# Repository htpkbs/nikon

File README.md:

# Overview

The nikon is a keyboard PCB.

It has:

* A column-staggered, ortholinear layout
* Low profile Kailh Choc switch spacing
* A split design
* Thumb key clusters
* USB-C
* Symmetry (the same PCB can be used for both left and right halves)

# v1.0 Notes

Capacitors `C1` and `C4` are mislabeled! The silkscreen labels are swapped.

# Key Layout

The key layout looks like this:

This is the raw data that can be pasted into [Keyboard Layout Editor](http://www.keyboard-layout-editor.com/):

```
[{x:3,c:"#2e2e2e",t:"#9c9c9c",a:7},"3",{x:8.5},"8"],
[{y:-0.875,x:2},"2",{x:10.5},"9"],
[{y:-0.875,x:4},"4",{x:6.5},"7"],
[{y:-0.875,x:5},"5",{x:4.5},"6"],
[{y:-0.875},"","1",{x:12.5},"0",""],
[{y:-0.625,x:6,h:1.5},"",{x:2.5,h:1.5},""],
[{y:-0.875,x:3},"E",{x:8.5},"I"],
[{y:-0.875,x:2},"W",{x:10.5},"O"],
[{y:-0.875,x:4},"R",{x:6.5},"U"],
[{y:-0.875,x:5},"T",{x:4.5},"Y"],
[{y:-0.875},"","Q",{x:12.5},"P",""],
[{y:-0.5,x:3},"D",{x:8.5},"K"],
[{y:-0.875,x:2},"S",{x:10.5},"L"],
[{y:-0.875,x:4},"F",{x:6.5},"J"],
[{y:-0.875,x:5},"G",{h:1.5},"",{x:2.5,h:1.5},"","H"],
[{y:-0.875},"","A",{x:12.5},";","'"],
[{y:-0.5,x:3},"C",{x:8.5},","],
[{y:-0.875,x:2},"X",{x:10.5},"."],
[{y:-0.875,x:4},"V",{x:6.5},"M"],
[{y:-0.875,x:5},"B",{x:4.5},"N"],
[{y:-0.875},"Shift","Z",{x:12.5},"/","Shift"],
[{y:-0.375,x:2},"",{x:10.5},""],
[{y:-0.625},"","",{x:12.5},"",""],
[{rx:7.5,ry:4,x:-4.5},""],
[{rx:9,x:3.5},""],
[{r:30,rx:7.5,y:0.75,x:-0.625,w:1.5},""],
[{x:-1.875,h:1.5},"",{h:1.5},"",{h:1.5},""],
[{r:-30,rx:9,y:0.75,x:-0.875,w:1.5},""],
[{x:-1.125,h:1.5},"",{h:1.5},"",{h:1.5},""]
```

# PCB Renders

# Case

Files are in the `case` directory.

# Schematic

[There is a PDF of the schematic here](assets/schematic.pdf).

# AVR Programming

To-do.

## QMK

The nikon uses a port expander (the ATmega MCP23018), similar to the ErgoDox. The firmware will likely be copied from the [Pterodactyl keyboard](https://github.com/qmk/qmk_firmware/tree/master/keyboards/handwired/pterodactyl) since that seems to be the most recent keyboard with a custom `matrix.c` and support for a port expander. Eventually hopefully there will be a [generalized matrix.c for keyboards that use I/O expanders](https://github.com/qmk/qmk_firmware/issues/2065).

# Sublicenses

* The Kailh Choc switch footprints are from the [keyswitch-kicad-libary repository](https://github.com/perigoso/keyswitch-kicad-library). [The CC BY 4.0 license is included here](LICENSE.keyswitch-kicad-library).
* The keyswitch symbols are modified versions from the [MX_Alps_Hybrid repository](https://github.com/ai03-2725/MX_Alps_Hybrid). [The MIT license is included here](LICENSE.MX_Alps_Hybrid).
* The TRRS jack symbol and footprint are not licensed by CUI Devices and are free to use.
* The USB jack symbol and footprint are from SnapEDA (linked from the GCT website) and do not appear to be licensed by GCT.
* The MCP23018 symbol and footprint are from Microchip and are subject to the Ultra Library terms and conditions, which state, "You may incorporate the CONTENT that you are authorized to access into your products or designs which may be distributed without restriction, including for commercial, educational, and open-source purposes."

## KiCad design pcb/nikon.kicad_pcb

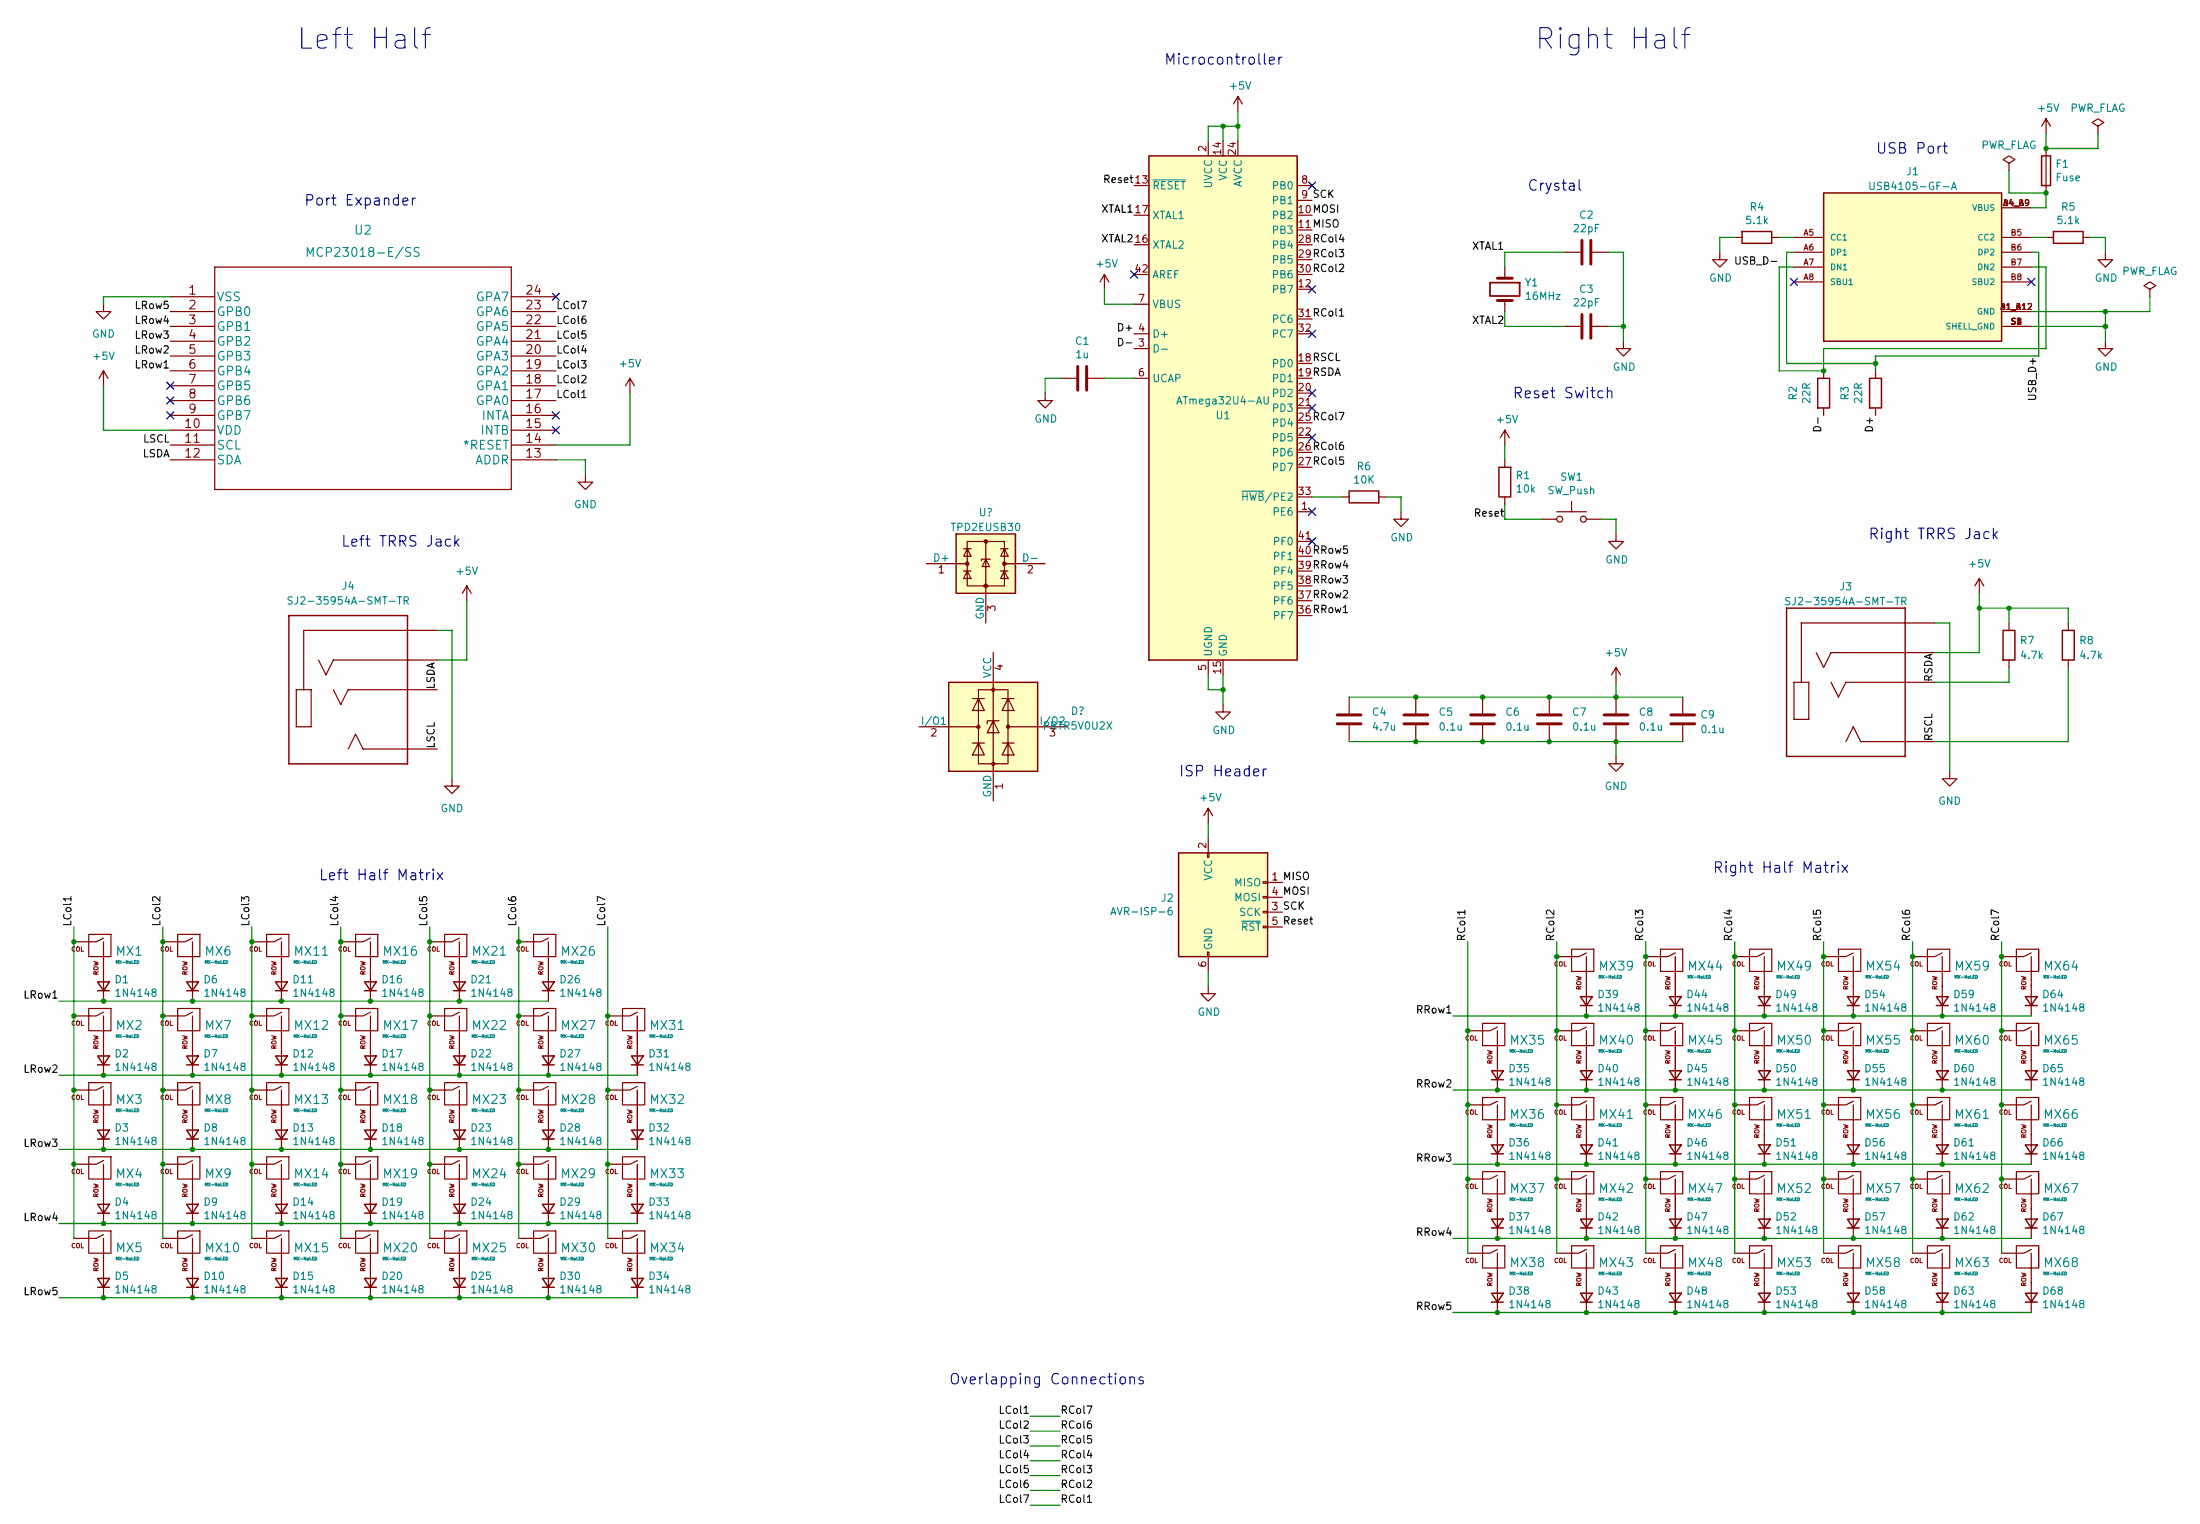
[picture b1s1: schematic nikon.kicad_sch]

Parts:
C1: 1u; C_0805_2012Metric_Pad1.18x1.45mm_HandSolder
C2, C3: 22pF; C_0805_2012Metric_Pad1.18x1.45mm_HandSolder
C4: 4.7u; C_0805_2012Metric_Pad1.18x1.45mm_HandSolder
C5, C6, C7, C8, C9: 0.1u; C_0805_2012Metric_Pad1.18x1.45mm_HandSolder
D1, D2, D3, D4, D5, D6, D7, D8, D9, D10, D11, D12, D13, D14, D15, D16, D17, D18, D19, D20, D21, D22, D23, D24, D25, D26, D27, D28, D29, D30, D31, D32, D33, D34, D35, D36, D37, D38, D39, D40, D41, D42, D43, D44, D45, D46, D47, D48, D49, D50, D51, D52, D53, D54, D55, D56, D57, D58, D59, D60, D61, D62, D63, D64, D65, D66, D67, D68: 1N4148; D_SOD-123F
F1: Fuse; Fuse_0805_2012Metric_Pad1.15x1.40mm_HandSolder
J1: USB4105-GF-A; GCT_USB4105-GF-A; PARTREV A3
J2: AVR-ISP-6; Tag-Connect_TC2030-IDC-NL_2x03_P1.27mm_Vertical
J3, J4: SJ2-35954A-SMT-TR; CUI_SJ2-35954A-SMT-TR; PARTREV 1.01
MX1, MX2, MX3, MX4, MX5, MX6, MX7, MX8, MX9, MX10, MX11, MX12, MX13, MX14, MX15, MX16, MX17, MX18, MX19, MX20, MX21, MX22, MX23, MX24, MX26, MX27, MX28, MX29, MX39, MX40, MX41, MX42, MX44, MX45, MX46, MX47, MX49, MX50, MX51, MX52, MX53, MX54, MX55, MX56, MX57, MX58, MX59, MX60, MX61, MX62, MX63, MX64, MX65, MX66, MX67, MX68: MX-NoLED; SW_Kailh_Choc_V1_1.00u
MX25, MX30, MX31, MX32, MX33, MX34, MX35, MX36, MX37, MX38, MX43, MX48: MX-NoLED; SW_Kailh_Choc_V1_1.50u
R1: 10k; R_0805_2012Metric_Pad1.20x1.40mm_HandSolder
R2, R3: 22R; R_0805_2012Metric_Pad1.20x1.40mm_HandSolder
R4, R5: 5.1k; R_0805_2012Metric_Pad1.20x1.40mm_HandSolder
R6: 10K; R_0805_2012Metric_Pad1.20x1.40mm_HandSolder
R7, R8: 4.7k; R_0805_2012Metric_Pad1.20x1.40mm_HandSolder
SW1: SW_Push; SW_Push_1P1T_NO_CK_KMR2
U1: ATmega32U4-AU; TQFP-44_10x10mm_P0.8mm
U2: MCP23018-E/SS; MCP23018-E&slash_SS
Y1: 16MHz; Crystal_SMD_Abracon_ABM3-2Pin_5.0x3.2mm_HandSoldering

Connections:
+5V: C4.1, C5.1, C6.1, C7.1, C8.1, C9.1, F1.1, J2.2 (VCC), J3.4, J4.4, R1.2, R7.1, R8.1, U1.2 (UVCC), U1.7 (VBUS), U1.14 (VCC), U1.24 (AVCC), U1.34 (VCC), U1.44 (AVCC), U2.10 (VDD), U2.14 (*RESET)
/D+: R3.2, U1.4 (D+)
/D-: R2.2, U1.3 (D-)
/LCol1: MX1.1 (COL), MX2.1 (COL), MX3.1 (COL), MX4.1 (COL), MX5.1 (COL), MX64.1 (COL), MX65.1 (COL), MX66.1 (COL), MX67.1 (COL), MX68.1 (COL), U1.25 (PD4), U2.17 (GPA0)
/LCol2: MX6.1 (COL), MX7.1 (COL), MX8.1 (COL), MX9.1 (COL), MX10.1 (COL), MX59.1 (COL), MX60.1 (COL), MX61.1 (COL), MX62.1 (COL), MX63.1 (COL), U1.26 (PD6), U2.18 (GPA1)
/LCol3: MX11.1 (COL), MX12.1 (COL), MX13.1 (COL), MX14.1 (COL), MX15.1 (COL), MX54.1 (COL), MX55.1 (COL), MX56.1 (COL), MX57.1 (COL), MX58.1 (COL), U1.27 (PD7), U2.19 (GPA2)
/LCol4: MX16.1 (COL), MX17.1 (COL), MX18.1 (COL), MX19.1 (COL), MX20.1 (COL), MX49.1 (COL), MX50.1 (COL), MX51.1 (COL), MX52.1 (COL), MX53.1 (COL), U1.28 (PB4), U2.20 (GPA3)
/LCol5: MX21.1 (COL), MX22.1 (COL), MX23.1 (COL), MX24.1 (COL), MX25.1 (COL), MX44.1 (COL), MX45.1 (COL), MX46.1 (COL), MX47.1 (COL), MX48.1 (COL), U1.29 (PB5), U2.21 (GPA4)
/LCol6: MX26.1 (COL), MX27.1 (COL), MX28.1 (COL), MX29.1 (COL), MX30.1 (COL), MX39.1 (COL), MX40.1 (COL), MX41.1 (COL), MX42.1 (COL), MX43.1 (COL), U1.30 (PB6), U2.22 (GPA5)
/LCol7: MX31.1 (COL), MX32.1 (COL), MX33.1 (COL), MX34.1 (COL), MX35.1 (COL), MX36.1 (COL), MX37.1 (COL), MX38.1 (COL), U1.31 (PC6), U2.23 (GPA6)
/LRow1: D1.1 (K), D6.1 (K), D11.1 (K), D16.1 (K), D21.1 (K), D26.1 (K), U2.6 (GPB4)
/LRow2: D2.1 (K), D7.1 (K), D12.1 (K), D17.1 (K), D22.1 (K), D27.1 (K), D31.1 (K), U2.5 (GPB3)
/LRow3: D3.1 (K), D8.1 (K), D13.1 (K), D18.1 (K), D23.1 (K), D28.1 (K), D32.1 (K), U2.4 (GPB2)
/LRow4: D4.1 (K), D9.1 (K), D14.1 (K), D19.1 (K), D24.1 (K), D29.1 (K), D33.1 (K), U2.3 (GPB1)
/LRow5: D5.1 (K), D10.1 (K), D15.1 (K), D20.1 (K), D25.1 (K), D30.1 (K), D34.1 (K), U2.2 (GPB0)
/LSCL: J4.2, U2.11 (SCL)
/LSDA: J4.3, U2.12 (SDA)
/MISO: J2.1 (MISO), U1.11 (PB3)
/MOSI: J2.4 (MOSI), U1.10 (PB2)
/RRow1: D39.1 (K), D44.1 (K), D49.1 (K), D54.1 (K), D59.1 (K), D64.1 (K), U1.36 (PF7)
/RRow2: D35.1 (K), D40.1 (K), D45.1 (K), D50.1 (K), D55.1 (K), D60.1 (K), D65.1 (K), U1.37 (PF6)
/RRow3: D36.1 (K), D41.1 (K), D46.1 (K), D51.1 (K), D56.1 (K), D61.1 (K), D66.1 (K), U1.38 (PF5)
/RRow4: D37.1 (K), D42.1 (K), D47.1 (K), D52.1 (K), D57.1 (K), D62.1 (K), D67.1 (K), U1.39 (PF4)
/RRow5: D38.1 (K), D43.1 (K), D48.1 (K), D53.1 (K), D58.1 (K), D63.1 (K), D68.1 (K), U1.40 (PF1)
/RSCL: J3.2, R8.2, U1.18 (PD0)
/RSDA: J3.3, R7.2, U1.19 (PD1)
/Reset: J2.5 (~RST), R1.1, SW1.1, U1.13 (~RESET)
/SCK: J2.3 (SCK), U1.9 (PB1)
/USB_D+: J1.A6 (DP1), J1.B6 (DP2), R3.1
/USB_D-: J1.A7 (DN1), J1.B7 (DN2), R2.1
/XTAL1: C2.2, U1.17 (XTAL1), Y1.1
/XTAL2: C3.2, U1.16 (XTAL2), Y1.2
GND: C1.2, C2.1, C3.1, C4.2, C5.2, C6.2, C7.2, C8.2, C9.2, J1.A1_B12 (GND), J1.B1_A12 (GND), J1.S1 (SHELL_GND), J1.S2 (SHELL_GND), J1.S3 (SHELL_GND), J1.S4 (SHELL_GND), J2.6 (GND), J3.1, J4.1, R4.2, R5.1, R6.2, SW1.2, U1.5 (UGND), U1.15 (GND), U1.23 (GND), U1.35 (GND), U1.43 (GND), U2.1 (VSS), U2.13 (ADDR)
unnamed: C1.1, U1.6 (UCAP)
unnamed: D1.2 (A), MX1.2 (ROW)
unnamed: D2.2 (A), MX2.2 (ROW)
unnamed: D3.2 (A), MX3.2 (ROW)
unnamed: D4.2 (A), MX4.2 (ROW)
unnamed: D5.2 (A), MX5.2 (ROW)
unnamed: D6.2 (A), MX6.2 (ROW)
unnamed: D7.2 (A), MX7.2 (ROW)
unnamed: D8.2 (A), MX8.2 (ROW)
unnamed: D9.2 (A), MX9.2 (ROW)
unnamed: D10.2 (A), MX10.2 (ROW)
unnamed: D11.2 (A), MX11.2 (ROW)
unnamed: D12.2 (A), MX12.2 (ROW)
unnamed: D13.2 (A), MX13.2 (ROW)
unnamed: D14.2 (A), MX14.2 (ROW)
unnamed: D15.2 (A), MX15.2 (ROW)
unnamed: D16.2 (A), MX16.2 (ROW)
unnamed: D17.2 (A), MX17.2 (ROW)
unnamed: D18.2 (A), MX18.2 (ROW)
unnamed: D19.2 (A), MX19.2 (ROW)
unnamed: D20.2 (A), MX20.2 (ROW)
unnamed: D21.2 (A), MX21.2 (ROW)
unnamed: D22.2 (A), MX22.2 (ROW)
unnamed: D23.2 (A), MX23.2 (ROW)
unnamed: D24.2 (A), MX24.2 (ROW)
unnamed: D25.2 (A), MX25.2 (ROW)
unnamed: D26.2 (A), MX26.2 (ROW)
unnamed: D27.2 (A), MX27.2 (ROW)
unnamed: D28.2 (A), MX28.2 (ROW)
unnamed: D29.2 (A), MX29.2 (ROW)
unnamed: D30.2 (A), MX30.2 (ROW)
unnamed: D31.2 (A), MX31.2 (ROW)
unnamed: D32.2 (A), MX32.2 (ROW)
unnamed: D33.2 (A), MX33.2 (ROW)
unnamed: D34.2 (A), MX34.2 (ROW)
unnamed: D35.2 (A), MX35.2 (ROW)
unnamed: D36.2 (A), MX36.2 (ROW)
unnamed: D37.2 (A), MX37.2 (ROW)
unnamed: D38.2 (A), MX38.2 (ROW)
unnamed: D39.2 (A), MX39.2 (ROW)
unnamed: D40.2 (A), MX40.2 (ROW)
unnamed: D41.2 (A), MX41.2 (ROW)
unnamed: D42.2 (A), MX42.2 (ROW)
unnamed: D43.2 (A), MX43.2 (ROW)
unnamed: D44.2 (A), MX44.2 (ROW)
unnamed: D45.2 (A), MX45.2 (ROW)
unnamed: D46.2 (A), MX46.2 (ROW)
unnamed: D47.2 (A), MX47.2 (ROW)
unnamed: D48.2 (A), MX48.2 (ROW)
unnamed: D49.2 (A), MX49.2 (ROW)
unnamed: D50.2 (A), MX50.2 (ROW)
unnamed: D51.2 (A), MX51.2 (ROW)
unnamed: D52.2 (A), MX52.2 (ROW)
unnamed: D53.2 (A), MX53.2 (ROW)
unnamed: D54.2 (A), MX54.2 (ROW)
unnamed: D55.2 (A), MX55.2 (ROW)
unnamed: D56.2 (A), MX56.2 (ROW)
unnamed: D57.2 (A), MX57.2 (ROW)
unnamed: D58.2 (A), MX58.2 (ROW)
unnamed: D59.2 (A), MX59.2 (ROW)
unnamed: D60.2 (A), MX60.2 (ROW)
unnamed: D61.2 (A), MX61.2 (ROW)
unnamed: D62.2 (A), MX62.2 (ROW)
unnamed: D63.2 (A), MX63.2 (ROW)
unnamed: D64.2 (A), MX64.2 (ROW)
unnamed: D65.2 (A), MX65.2 (ROW)
unnamed: D66.2 (A), MX66.2 (ROW)
unnamed: D67.2 (A), MX67.2 (ROW)
unnamed: D68.2 (A), MX68.2 (ROW)
unnamed: F1.2, J1.A4_B9 (VBUS), J1.B4_A9 (VBUS)
unnamed: J1.A5 (CC1), R4.1
unnamed: J1.B5 (CC2), R5.2
unnamed: R6.1, U1.33 (~HWB/PE2)

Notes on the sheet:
Left TRRS Jack
Reset Switch
Right TRRS Jack
Left Half
Right Half
Microcontroller
Overlapping Connections
Crystal
Port Expander
Left Half Matrix
ISP Header
Right Half Matrix
USB Port

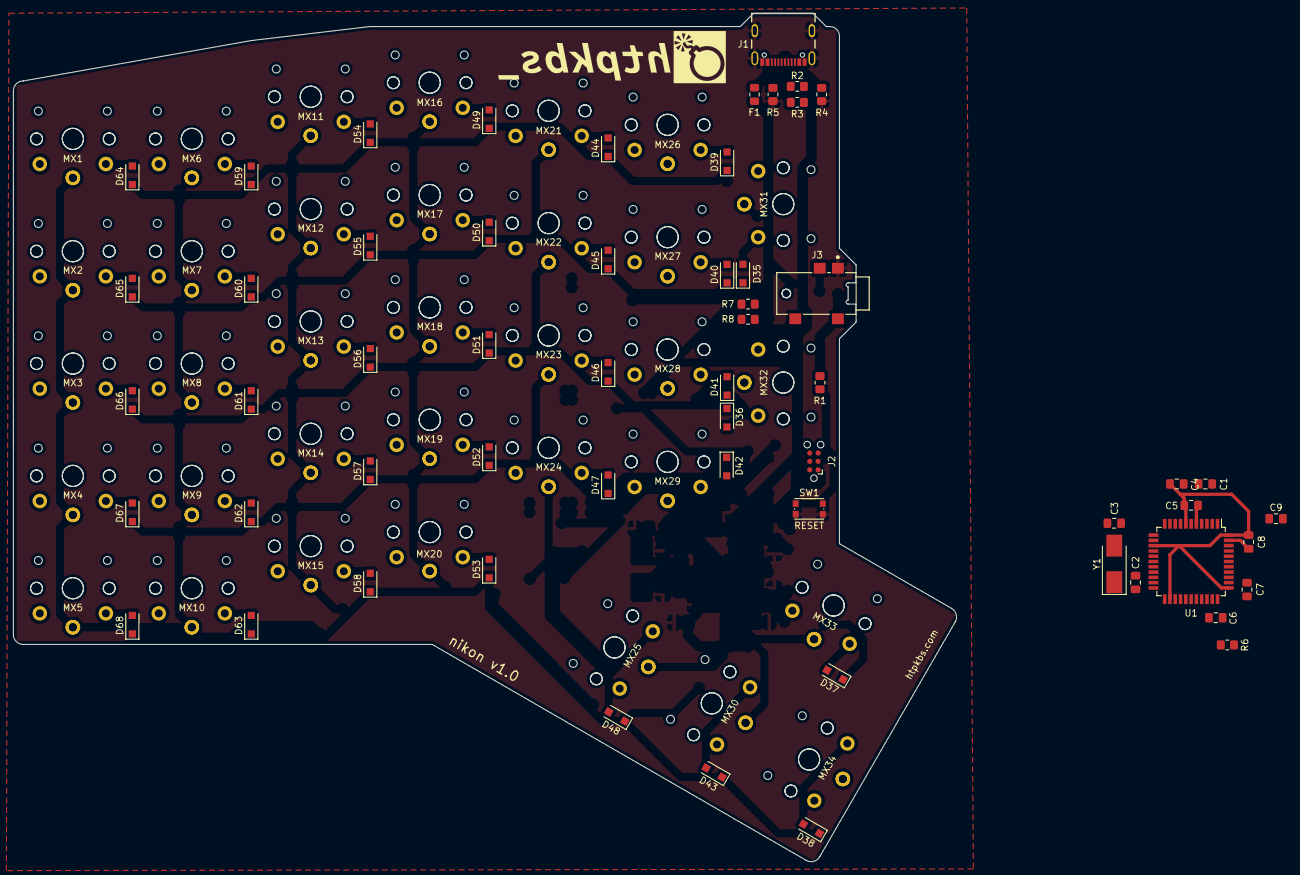
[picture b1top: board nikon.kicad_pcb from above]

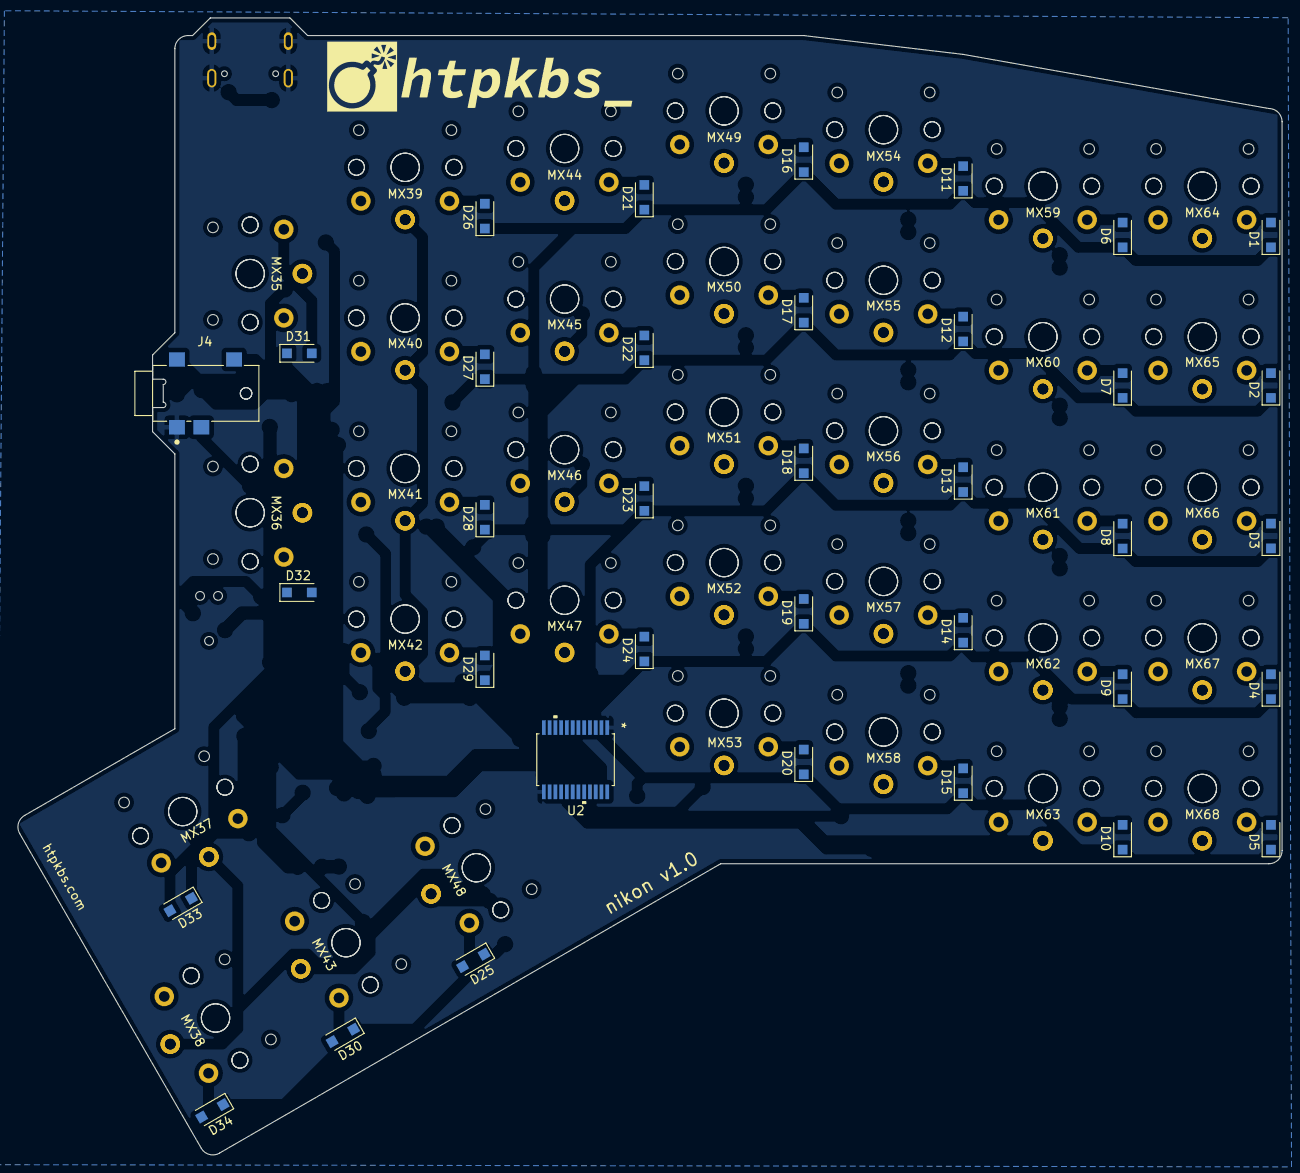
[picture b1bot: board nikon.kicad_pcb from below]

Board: 2 copper layers, 142.7 x 128.4 mm, 162 parts (70 on the bottom side), 106 nets.

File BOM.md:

# Bill of Materials

J2 (the Tag-Connect ISP headers) and MX1-MX68 (the key switches) are not included.

Since the PCB is reversible, the BOM is split up between the left and right halves. To build a full keyboard, you need the components for both halves.

## Left Half

| Reference | Quantity | Value | Link |
| --- | --- | --- | --- |
| D1-D34 | 34 | 1N4148 | https://www.digikey.com/en/products/detail/taiwan-semiconduc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 |
| J4 | 1 | SJ2-35954-SMT-TR | https://www.digikey.com/en/products/detail/cui-devices/SJ2-3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 |
| U2 | 1 | MCP23018-E/SS | https://www.digikey.com/en/products/detail/microchip-technol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 |

## Right Half

| Reference | Quantity | Value | Link |
| --- | --- | --- | --- |
| C1 | 1 | 1u | https://www.digikey.com/en/products/detail/avx-corporation/0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 |
| C2, C3 | 2 | 22pF | https://www.digikey.com/en/products/detail/avx-corporation/0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 |
| C4 | 1 | 4.7u | https://www.digikey.com/en/products/detail/avx-corporation/0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 |
| C5-C8 | 4 | 0.1u | https://www.digikey.com/en/products/detail/avx-corporation/0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 |
| D35-D68 | 34 | 1N4148 | https://www.digikey.com/en/products/detail/taiwan-semiconduc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
| F1 | 1 | 100mA | https://www.digikey.com/en/products/detail/littelfuse-inc/08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 |
| J1 | 1 | USB4105-GF-A | https://www.digikey.com/en/products/detail/gct/USB4105-GF-A/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 |
| J3 | 1 | SJ2-35954-SMT-TR | https://www.digikey.com/en/products/detail/cui-devices/SJ2-3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 |
| R1, R6 | 2 | 10k | https://www.digikey.com/en/products/detail/bourns-inc/CR0805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 |
| R2, R3 | 2 | 22R | https://www.digikey.com/en/products/detail/bourns-inc/CR0805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 |
| R4, R5 | 2 | 5.1k | https://www.digikey.com/en/products/detail/bourns-inc/CR0805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 |
| R7, R8 | 2 | 4.7k | https://www.digikey.com/en/products/detail/bourns-inc/CR0805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 |
| SW1 | 1 | Reset | https://www.digikey.com/en/products/detail/c-k/KMR241NG-LFS/2176486 |
| U1 | 1 | ATmega32U4-AU | https://www.digikey.com/en/products/detail/microchip-technol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 |
| Y1 | 1 | 16MHz | https://www.digikey.com/en/products/detail/abracon-llc/ABM3-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 |

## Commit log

2022-02-28 both halves
2022-03-10 pre-flippable
2022-03-12 remove right pcb
2022-03-12 license
2022-03-12 pics
2022-03-12 middle
2022-03-12 no more notes
2022-03-12 add bom
2022-03-13 ignore

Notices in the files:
pcb/nikon.kicad_pcb:
License: BSD 2-Clause
parts and their libraries:
Copyright 2021 Accelerated Designs. All rights reserved.
